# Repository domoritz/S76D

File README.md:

# S76D #
S76D stands for _Singing Very High Speed Integrated Circuit Hardware Description Language Board_

## Description ##
The main file is `MusicPlayer.vhd`.

The dream of every geeky hardware hacker has come true. We build a working MMC/SD card reader, block ram buffer and a music player with a 12 DAC (Digital-Analog Converter) Bit for Mono WAV/RIFF on a Spartan 3 FPGA. The Hardware is implemented in VHDL which is a hardware description language. This means that everything is implemented in hardware and not software. 

This Project started as a student project a few months ago and today we were able to play the first song. Hope you like it as much as we enjoyed finally hearing the board singing.

If you want to know a little bit (:-P) more about the project or see nice picures go to [this blog post](http://domoritz.de/blog/2012/03/singing_vhdl_board/) (German)

Demo video on [YouTube](http://www.youtube.com/watch?v=qsjFVgriZzY).

### Features ###
* MMC Card reader via SPI interface
* plays Mono WAV/RIFF
* DAC controller
* PS/2 controller
* two octave keyboard
* uses block ram fifo

## Documentation ##
Take a look at the content of the folder `docs`.

* Easy to understand [Introduction to MMC/SD Cards (German)](http://www.ifas.htwk-leipzig.de/easytoweb/download/D&E_11_2006_Anbindung_von_SD-Karten.pdf)
* Samsung's [MMC Product Datasheet](http://html.alldatasheet.com/html-pdf/141187/SAMSUNG/MC2GH512NMCA-2SA00/305/1/MC2GH512NMCA-2SA00.html) which is really helpful and a great reference.

## Status ##
Working but needs documentation.

## Dependencies ##
* Custom board (see folder `schematics`)
* PS2 keyboard
* MMC (multimedia card)

## Tested on this hardware ##
* Spartan-3 Starter Kit Board (Digilent Inc.), with Xilinx Spartan 3 FPGA (200k gates)

## Developer ##
* Kai Fabian
* Dominik Moritz

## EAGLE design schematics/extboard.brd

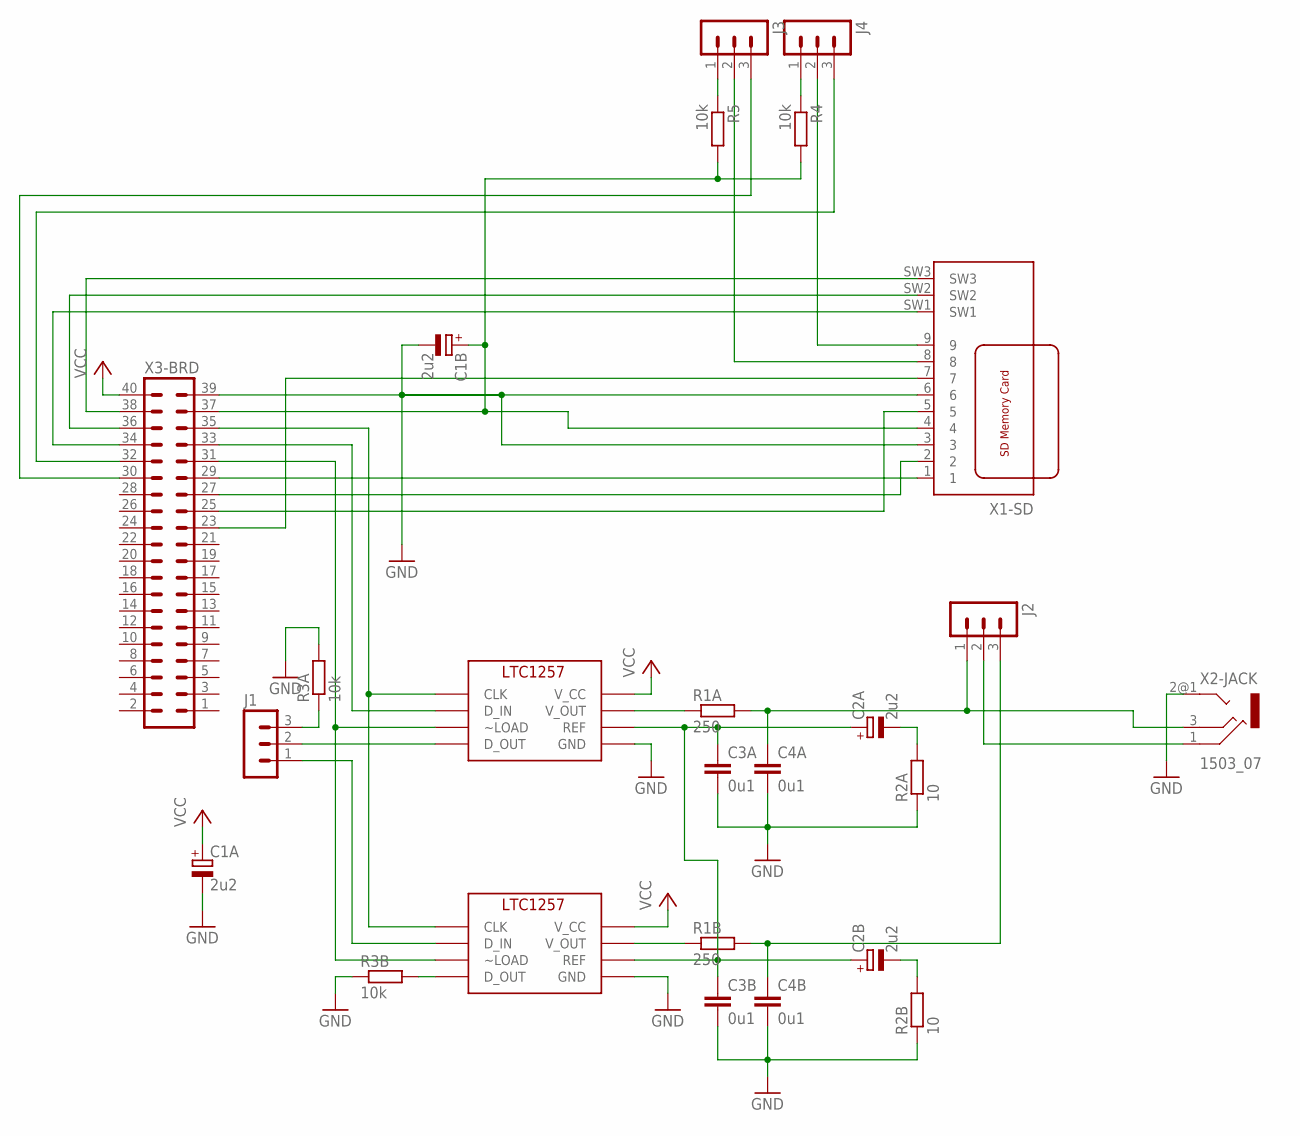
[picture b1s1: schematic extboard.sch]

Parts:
C1A, C1B, C2A, C2B: 2u2; E2,5-7
C3A, C3B, C4A, C4B: 0u1; C050-025X075
J1, J2, J3, J4: MA03-1
R1A, R1B: 250; 0207/10
R2A, R2B: 10; 0207/10
R3A, R3B, R4, R5: 10k; 0207/10
U1, U2: LTC1257; DIL-8
X1-SD: SDBMF; SDBMF-009XXBXX2
X2-JACK: 1503_07
X3-BRD: MA20-2W

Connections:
GND: C1A.-, C1B.-, C3A.2, C3B.2, C4A.2, C4B.2, R2A.1, R2B.1, R3A.2, R3B.1, U1.P$5 (GND), U2.P$5 (GND), X1-SD.3, X1-SD.6, X2-JACK.2@1 (2), X3-BRD.39
unnamed: U1.P$1 (CLK), U2.P$1 (CLK), X3-BRD.35
unnamed: U1.P$2 (D_IN), X3-BRD.33
unnamed: U1.P$3 (~LOAD), U2.P$3 (~LOAD), X3-BRD.31
unnamed: J1.1, U2.P$2 (D_IN)
unnamed: C2A.-, R2A.2
unnamed: C2A.+, C2B.+, C3A.1, C3B.1, U1.P$6 (REF), U2.P$6 (REF)
unnamed: C4A.1, J2.1, R1A.2, X2-JACK.3
unnamed: R1A.1, U1.P$7 (V_OUT)
unnamed: C1B.+, R4.2, R5.2, X1-SD.4, X3-BRD.37
unnamed: J3.1, R5.1
unnamed: X1-SD.1, X3-BRD.29
unnamed: X1-SD.2, X3-BRD.27
unnamed: X1-SD.5, X3-BRD.25
unnamed: X1-SD.7, X3-BRD.23
unnamed: J1.3, R3A.1
unnamed: J1.2, U1.P$4 (D_OUT)
unnamed: J2.2, X2-JACK.1
unnamed: R3B.2, U2.P$4 (D_OUT)
unnamed: C4B.1, J2.3, R1B.2
unnamed: R1B.1, U2.P$7 (V_OUT)
unnamed: C2B.-, R2B.2
unnamed: X1-SD.SW1, X3-BRD.34
unnamed: X1-SD.SW2, X3-BRD.36
unnamed: X1-SD.SW3, X3-BRD.38
unnamed: J4.1, R4.1
unnamed: J3.2, X1-SD.8
unnamed: J4.2, X1-SD.9
unnamed: J4.3, X3-BRD.32
unnamed: J3.3, X3-BRD.30
VCC: C1A.+, U1.P$8 (V_CC), U2.P$8 (V_CC), X3-BRD.40

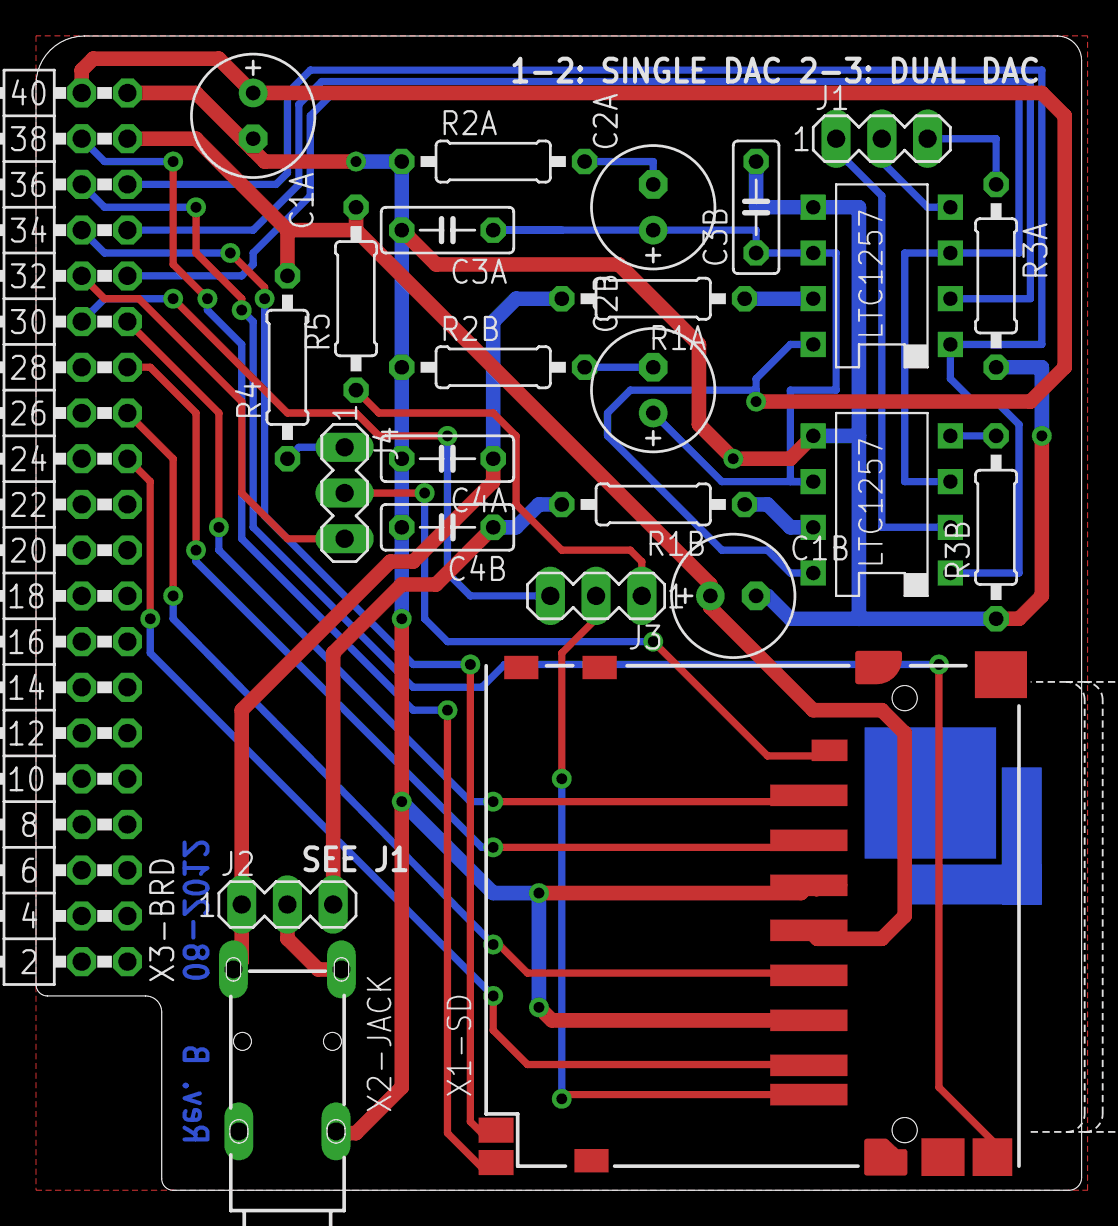
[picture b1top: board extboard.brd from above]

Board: 2 copper layers, 58.1 x 64.1 mm, 25 parts (0 on the bottom side), 31 nets.

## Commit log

2012-04-11 added develper notice to readme
2012-04-11 more descriptions in readme
2012-05-06 move sources to src directory
2012-05-06 Add overview documents for documentation
2012-05-06 Added references to great documents
2012-05-06 cleanup of comments
2012-05-10 ampersand in url
2012-05-30 added necessary files for deplyment on spartan board
2012-05-30 updated header for proper attribution
2012-05-30 user guide for modes
2012-06-08 how to use keyboard
    added user guide entry
2012-07-02 Added old development version
2012-07-02 Added authors to RectWaveSynth.vhd
2012-07-02 Fixed test board name
2012-07-02 schematics: PCB draft
2012-07-05 fix in project
2012-07-05 Revert "fix in project"
    This reverts commit c547f6f15a4990d6566c24fb7aa512bb4a2c580e.
2012-07-05 fix project file
2012-07-05 Documentation on MMC Card
2012-07-05 show status of mmc reader
2012-07-05 added notes on schematics
2012-07-05 How to bring data onto the SD/MMC card
2012-07-05 gitignore
2012-07-05 Removed Thumbs.db
2012-07-05 Musicplayer bitstream
2012-07-24 code overview fix
2012-07-24 fsm for mmc controller
2012-07-24 schematics: board rev. A
2012-07-24 added transtion conditions
2012-07-24 schematics: Fix in Rev A
2012-07-24 schematics: part list for Rev A + partial suppliers
2012-07-24 flow chart for reading
2012-08-01 schematics: next iteration
2012-08-01 Moves doc sources to subdir, graphviz makefile
2012-08-01 fixed makefile
2012-08-01 better charts
2012-08-01 schematic: Revision A iteration - jumpers for connecting DATA2 and DATA3 to board
2012-08-01 translated comment
2012-08-01 latex documentation
2012-08-01 More images in doc
2012-08-01 Some notes on commands
2012-08-01 schematics: Elevated to Revision B (2 prototypes in production)
2012-08-01 schematics: Rev. B images
2012-08-01 schematics: Do not ignore .zip files anymore
2012-08-01 schematics: Revision B production files
2012-08-01 schematics: Added render of Rev. B
2012-08-02 Added rendered image to doc
2012-08-10 A little bit more text in the docs
2012-08-26 small fixes
2012-08-26 Overview of the whole structure
2013-04-12 structure diagram, next iteration
2013-05-12 Fix little error in mmc controller flow
2013-05-12 Extend documentation document
2013-05-12 Fix link in readme
2013-05-12 Docs: Audio/DAC area iteration
2013-05-12 Docs: Audio/DAC area iteration (II)
2013-05-14 Improve layout if structure diagram
2013-07-11 docs: Next iteration of overview structure diagram
